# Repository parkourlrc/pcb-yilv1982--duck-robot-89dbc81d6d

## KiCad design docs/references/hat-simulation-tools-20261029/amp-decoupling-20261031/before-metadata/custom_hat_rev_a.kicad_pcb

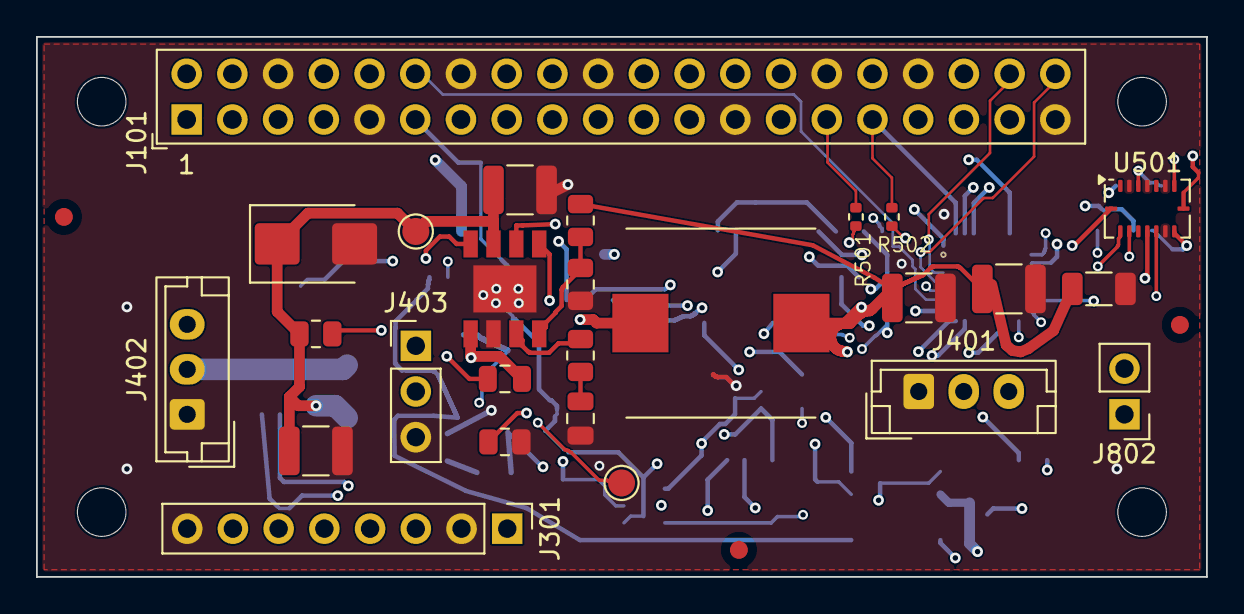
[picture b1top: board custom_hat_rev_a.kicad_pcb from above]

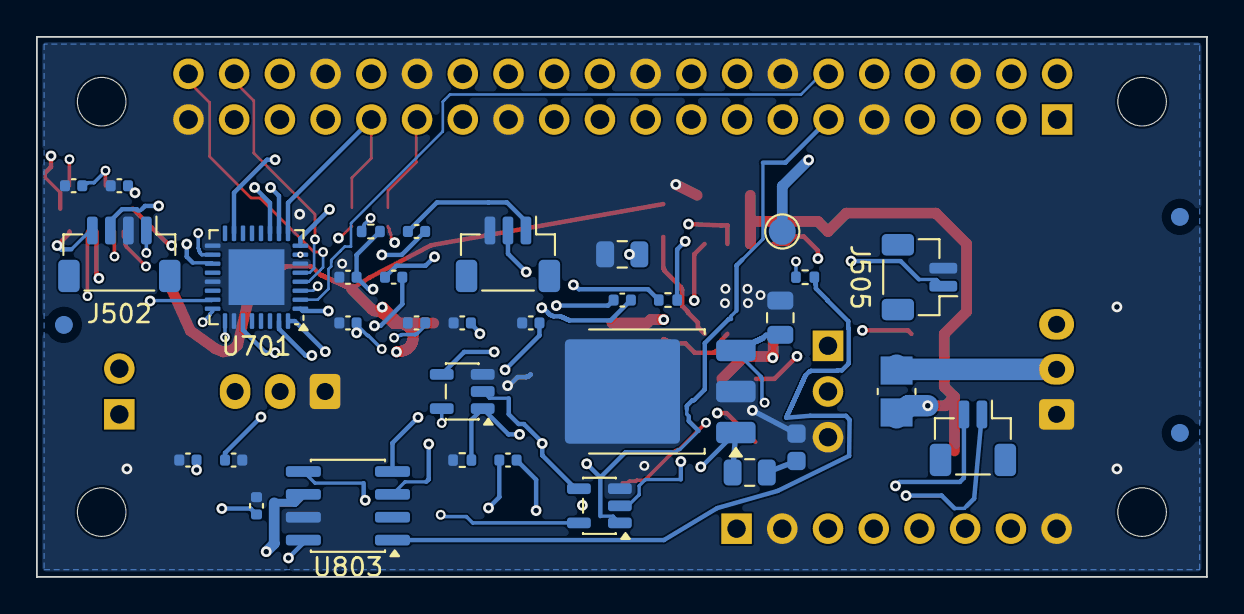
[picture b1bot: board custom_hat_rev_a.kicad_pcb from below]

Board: 4 copper layers, 65.0 x 30.0 mm, 69 parts (36 on the bottom side), 42 nets.

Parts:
C301: 3.3nF; C_0805_2012Metric
C302: 100nF; C_0805_2012Metric
C303, C304, C305, C306: 22uF; C_1210_3225Metric
C307: 22uF reserve; C_1206_3216Metric
C308, C309: 2.2uF; C_0805_2012Metric
C310, C312, C319, C320, C327: 100nF; C_0402_1005Metric
C311, C313, C315, C321, C322, C325, C326: 1uF; C_0402_1005Metric
C317, C318: 10uF; C_0402_1005Metric
C323: 10uF; C_0805_2012Metric
D301: SMBJ12A (fitted); D_SMB
FID1, FID2, FID3, FID4, FID5, FID6: Fiducial_1mm_Mask2mm
H1, H2: MountingHole_2.7mm_M2.5; MountingHole_2.7_M2.5_Head4.5
H3, H4: MountingHole_2.7mm_M2.5
J101: RADXA_ZERO_3W_40P; Radxa40P_Samtec_SSW120
J301: POWER_AND_RAILS; Samtec_TSW108_07
J401: DYNAMIXEL_TTL_1; JST_EH_B3B-EH-A_1x03_P2.50mm_Vertical
J402: DYNAMIXEL_TTL_2; JST_EH_B3B-EH-A_1x03_P2.50mm_Vertical
J403: HOST_UART2; Samtec_TSW103_07
J502: TOF_I2C5; JST_SH_BM04B-SRSS-TB_1x04-1MP_P1.00mm_Vertical
J504: AUDIO_OUT_SH; JST_SH_BM03B-SRSS-TB_1x03-1MP_P1.00mm_Vertical
J505: MIC_IN; JST_SH_BM02B-SRSS-TB_1x02-1MP_P1.00mm_Vertical
J506: SPEAKER; JST_SH_BM02B-SRSS-TB_1x02-1MP_P1.00mm_Vertical
J802: IMU_INT_TP; Samtec_TSW102_07
L301: 5.6uH; IHLP4040DZ_5A_Above2u2
R301: 52.3k; R_0805_2012Metric
R302: 10k; R_0805_2012Metric
R303: 200k; R_0805_2012Metric
R304: 14k; R_0805_2012Metric
R305: 100k; R_0805_2012Metric
R308: 10k; R_0402_1005Metric
R309: 0R; Vishay_WSL1206_Jumper
R310, R311: 100k; R_0402_1005Metric
R312: 2.2k; R_0402_1005Metric
R501, R502: 4.7k; R_0402_1005Metric
R703: 0.047; Vishay_WSLP0603_Damping
TP801: VBATT_2S_IN; TestPoint_Pad_D1.5mm
TP802: +5V; TestPoint_Pad_D1.5mm
TP803: +3V3; TestPoint_Pad_D1.5mm
U301: AP64350; SO-8EP_AP64350
U501: BMI088; Bosch_LGA-16_4.5x3mm_P0.5mm_LayoutBorder7x1y_ClockwisePinNu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
U701: TLV320AIC3104; VQFN-32-1EP_5x5mm_P0.5mm_EP3.1x3.1mm
U702: LP38691DT-1.8; TO-252-3_TabPin2
U801: SN74LVC1G126; SOT-23-5
U802: SN74LVC1G125; SOT-23-5
U803: PAM8302A; SOIC-8_3.9x4.9mm_P1.27mm

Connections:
+1V8_CODEC: C309.1, C311.1, J301.6, U701.32, U702.1
+3V3: C308.1, C312.1, C313.1, C315.1, C319.1, C320.1, J101.1, J101.17, J301.4, J502.1, R308.2, R311.2, R501.1, R502.1, TP803.1, U501.3, U501.7, U501.11, U501.14, U501.15, U701.7, U701.18, U701.24, U701.25, U702.3, U801.5, U802.5
+5V: C305.1, C306.1, C307.1, C323.1, J101.2, J101.4, J301.3, L301.2, R301.1, TP802.1, U803.6
+5V_FB: R301.2, R302.1, U301.5
AUDIO_AMP_EN: R311.1, U803.1
AUDIO_AMP_INN: C322.1, U803.4
AUDIO_AMP_INP: C321.2, U803.3
AUDIO_HP_L: C317.1, U701.19
AUDIO_HP_R: C318.1, U701.23
AUDIO_L: C317.2, J504.1
AUDIO_LINE_L: C321.1, U701.27
AUDIO_MIC: C325.1, J505.1, R312.2
AUDIO_MIC_AC: C325.2, U701.10
AUDIO_MIC_BIAS: C327.1, R312.1, U701.15
AUDIO_MIC_REF: C326.2, U701.11
AUDIO_R: C318.2, J504.2
BMI_INT1_TP: J802.1, U501.16
BMI_INT3_TP: J802.2, U501.12
BUCK_BST: C302.1, U301.1
BUCK_COMP: R304.1, U301.6
BUCK_EN: R305.2, U301.3
BUCK_RT: R303.1, U301.4
BUCK_SW: C302.2, L301.1, U301.8
CODEC_RST: C310.1, R308.1, U701.31
COMP_RC: C301.1, R304.2
DXL_DATA: J401.3, J402.3, U801.4, U802.2
DXL_DIR: J101.11, R310.1, U801.1, U802.1
I2C5_SCL: J101.29, J502.3, R501.2, U501.8, U701.8
I2C5_SDA: J101.31, J502.4, R502.2, U501.9, U701.9
I2S_BCLK: J101.12, U701.2
I2S_LRCK: J101.35, U701.3
I2S_MCLK: J101.13, U701.1
I2S_SDI: J101.38, U701.5
I2S_SDO: J101.40, U701.4
LDO_CAP_RETURN: C309.2, R703.1
POWER_GND: C301.2, C303.2, C304.2, C305.2, C306.2, C307.2, C308.2, C310.2, C311.2, C312.2, C313.2, C315.2, C319.2, C320.2, C322.2, C323.2, C326.1, C327.2, D301.2, J101.6, J101.9, J101.14, J101.20, J101.25, J101.30, J101.34, J101.39, J301.2, J301.8, J401.1, J402.1, J403.3, J502.2, J504.3, J505.2, R302.2, R303.2, R310.2, R703.2, U301.7, U301.9, U501.2, U501.4, U501.6, U501.10, U701.6, U701.17, U701.21, U701.26, U701.33, U702.2, U801.3, U802.3, U803.7
SERVO_VBAT: J301.7, J401.2, J402.2, R309.2
SPK_N: J506.2, U803.8
SPK_P: J506.1, U803.5
UART2_RX: J101.10, J403.2, U802.4
UART2_TX: J101.8, J403.1, U801.2
VBATT_2S_IN: C303.1, C304.1, D301.1, J301.1, R305.1, R309.1, TP801.1, U301.2
